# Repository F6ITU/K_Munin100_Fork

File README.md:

# MUNIN-100
MUNIN 100 is a 100W HF Power Amplifier using the MRF101AN/MRF101BN at 48V DC supply voltage.

Munin amps belongs to the OpenHPSDR familly

Original design by Kjell LA2NI

Some small mods by f6itu (just some kicad settings and design)

This amplifier board is part of a set consisting of a 100 W LD-Mos based RF power amplifier (Munin 100), 
a medium power Zolotarev low pass filter (600 or 1500 W), an Automatic Antenna Tuner (ATU) nickname « Aries » 
and a 4 port antenna switch.

But the power level is compatible with the traditional "Alexiares" filter frontend, (https://wiki.electrolab.fr/Projets:Lab:2017:Peripheriques_Angelia )
in lpf/hpf configuration or it's up to date evolution (lpf and dual bpf) 

All these developments are the work and intellectual property of Kjell Karlsen LA2NI and Laurence Barker G8NJJ.

This original work can be downloaded from

https://github.com/LA2NI/

https://github.com/laurencebarker

This board was originally developed in 2022 by Kjell LA2NI.

This fork (convertion/translation) is placed under the CERN Open source/ Open hardware Licence.

Kicad is an Opensource EDA software maintained by the European Reseach Center CERN (Conseil européen pour la recherche nucléaire)

The original work is protected by the TAPR Open Hardware licence

Mythology and openHPSDR codename conventions

Munin and Hugin are the two "messenger" ravens of the Norse god Odin - just as Hermes is the messenger-god in Greek mythology, 
and the masterpiece of the OpenHPSDR architecture 

This LDMoS transistor-based amplifier brings speech over the great distances of the "Midgard" of the waves

# Work in progress

Use these files at your own risk (that's the moto of ham homebrew)

As far as I know, this amp has never been build. Some minor KiCad errors and design hickups have been fix

The  the 1:4 input impedance transformer could be replaced with a simple coax strap (with or without ferrite core) as the combined impedance of the two transistors is approximately 50 Ohms at 55 MHz. On lower frequencies, the value of Z
is determined by the value of R4-R11 (22 Ohms, not yet tested) 

the pcb has been design to accomodate two feedback techniques : 
- coupling from a "secondary" winding in the first TLT
- or direct pickup of the drain signal fia a C & R feedback circuit

Value or R16/19 should be changed accordingly 

the first TLT MUST be soldered as short as possible. That's the reason why the third beta of this pcb uses a fat power trace located on the bottom Cu side of the board. 

For more information, please consider reading 

https://ludens.cl/Electron/50Wamp/50Wamp.html

and 

https://ludens.cl/Electron/RFamps/RFamps.html

(chapter "Broadband push-pull amplifiers"

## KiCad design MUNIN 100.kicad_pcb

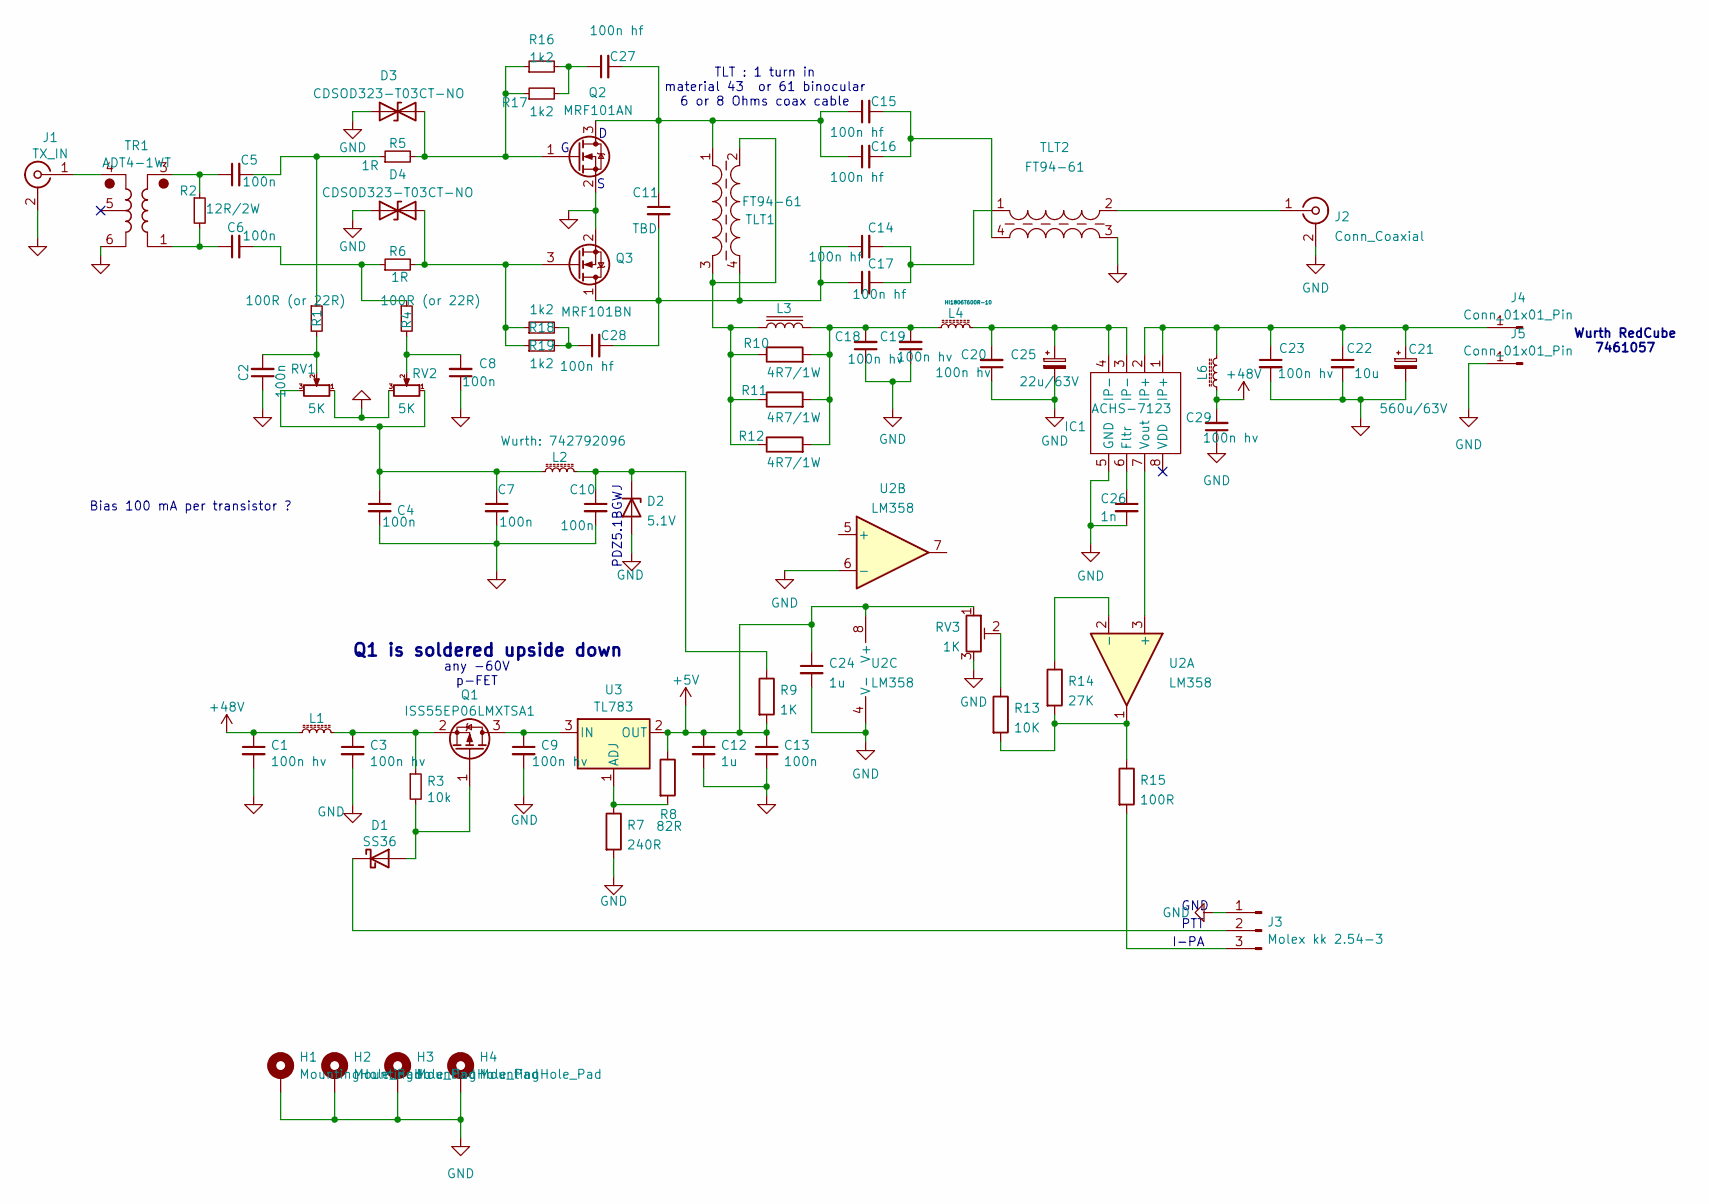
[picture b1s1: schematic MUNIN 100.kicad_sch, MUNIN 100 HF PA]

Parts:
C1, C3, C9, C18, C19, C20, C23, C29: 100n hv; C_0805_2012Metric_Pad1.18x1.45mm_HandSolder
C2, C4, C5, C6, C7, C8, C10, C13: 100n; C_0805_2012Metric_Pad1.18x1.45mm_HandSolder
C11: TBD; C_1210_3225Metric
C12, C24: 1u; C_0805_2012Metric_Pad1.18x1.45mm_HandSolder
C14, C15, C16, C17, C27, C28: 100n hf; C_1210_3225Metric_Pad1.33x2.70mm_HandSolder
C21: 560u/63V; CP_Elec_16x17.5
C22: 10u; C_0805_2012Metric_Pad1.18x1.45mm_HandSolder
C25: 22u/63V; CP_Elec_10x14.3
C26: 1n; C_0805_2012Metric_Pad1.18x1.45mm_HandSolder
D1: SS36; D_SOD-323_HandSoldering
D2: 5.1V; D_SOD-123F
D3, D4: CDSOD323-T03CT-NO; D_0805_2012Metric
H1, H2, H3, H4: MountingHole_Pad; MountingHole_3.2mm_M3_Pad_Via
IC1: ACHS-7123; SO-8_5.3x6.2mm_P1.27mm
J1: TX_IN; SMA_PINS
J2: Conn_Coaxial; SMA_PINS
J3: Molex kk 2.54-3; Molex_KK-254_AE-6410-03A_1x03_P2.54mm_Vertical
J4, J5: Conn_01x01_Pin; 7461057
L1: 742792096; L_0805_2012Metric_Pad1.05x1.20mm_HandSolder
L2: Wurth: 742792096; L_0805_2012Metric_Pad1.05x1.20mm_HandSolder
L3: FT-50-43; T50_V_smd
L4: HI1806T600R-10; L_1812_4532Metric
L6: L_Core_Ferrite_Small; L_0805_2012Metric_Pad1.05x1.20mm_HandSolder
Q1: ISS55EP06LMXTSA1; SOT-23
Q2: MRF101AN; TO-220-3_Horizontal_TabDown_SMD
Q3: MRF101BN; TO-220-3_Horizontal_TabDown_SMD
R1, R4: 100R (or 22R); R_0805_2012Metric_Pad1.20x1.40mm_HandSolder
R2: 12R/2W; R_2512_6332Metric
R3: 10k; R_0805_2012Metric_Pad1.20x1.40mm_HandSolder
R5, R6: 1R; R_0805_2012Metric_Pad1.20x1.40mm_HandSolder
R7: 240R; R_0805_2012Metric_Pad1.20x1.40mm_HandSolder
R8: 82R; R_0805_2012Metric_Pad1.20x1.40mm_HandSolder
R9: 1K; R_0805_2012Metric_Pad1.20x1.40mm_HandSolder
R10, R11, R12: 4R7/1W; R_1210_3225Metric
R13: 10K; R_0805_2012Metric_Pad1.20x1.40mm_HandSolder
R14: 27K; R_0805_2012Metric_Pad1.20x1.40mm_HandSolder
R15: 100R; R_0805_2012Metric_Pad1.20x1.40mm_HandSolder
R16, R17, R18, R19: 1k2; R_1206_3216Metric
RV1, RV2: 5K; Potentiometer_Bourns_3214X_Vertical
RV3: 1K; Potentiometer_Bourns_3214X_Vertical
TLT1: FT94-61; TLT
TLT2: FT94-61; Dual_FB-61-4852
TR1: ADT4-1WT; Mini-Circuits_CD542_H2.84mm
U2: LM358; SOIC-8_3.9x4.9mm_P1.27mm
U3: TL783; TO-263-3_TabPin2

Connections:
+5V: C12.1, C13.1, C24.1, R8.1, R9.2, RV3.1, U2.8 (V+), U3.2 (OUT)
+48V: C1.1, C29.2, L1.1, L6.1
GND: C1.2, C2.1, C3.2, C4.2, C7.2, C8.1, C9.2, C10.2, C12.2, C13.2, C18.1, C19.1, C20.1, C21.2, C22.2, C23.2, C24.2, C25.2, C26.2, C29.1, D2.2 (A), D3.1 (A1), D4.1 (A1), H1.1, H2.1, H3.1, H4.1, IC1.5 (GND), J1.2 (Ext), J2.2 (Ext), J3.1, J5.1, Q2.2 (S), Q3.2 (S), R7.2, RV1.1, RV2.3, RV3.3, TLT2.3, TR1.6, U2.4 (V-), U2.6 (-)
unnamed: C2.2, R1.2, RV1.2
unnamed: C4.1, C7.1, L2.1, RV1.3, RV2.1
unnamed: C5.1, R2.1, TR1.3
unnamed: C5.2, R1.1, R5.1
unnamed: C6.1, R2.2, TR1.1
unnamed: C6.2, R4.1, R6.1
unnamed: C8.2, R4.2, RV2.2
unnamed: C14.2, C17.2, TLT2.1
unnamed: C15.2, C16.2, TLT2.4
unnamed: C18.2, C19.2, L3.2, L4.1, R10.2, R11.2, R12.2
unnamed: C20.2, C25.1, IC1.3 (IP-), IC1.4 (IP-), L4.2
unnamed: C27.1, R16.2, R17.2
unnamed: C28.1, R18.2, R19.2
unnamed: D1.2 (A), Q1.1 (G), R3.2
unnamed: D1.1 (K), J3.2
unnamed: C10.1, D2.1 (K), L2.2, R9.1
unnamed: D3.2 (A2), Q2.1 (G), R5.2, R16.1, R17.1
unnamed: D4.2 (A2), Q3.3 (G), R6.2, R18.1, R19.1
unnamed: C26.1, IC1.6 (Fltr)
unnamed: IC1.7 (Vout), U2.3 (+)
unnamed: J1.1 (In), TR1.4
unnamed: J2.1 (In), TLT2.2
unnamed: J3.3, R15.2
unnamed: C21.1, C22.1, C23.1, IC1.1 (IP+), IC1.2 (IP+), J4.1, L6.2
unnamed: L3.1, R10.1, R11.1, R12.1, TLT1.2, TLT1.3
unnamed: C9.1, Q1.3 (D), U3.3 (IN)
unnamed: C3.1, L1.2, Q1.2 (S), R3.1
unnamed: C11.1, C15.1, C16.1, C27.2, Q2.3 (D), TLT1.1
unnamed: C11.2, C14.1, C17.1, C28.2, Q3.1 (D), TLT1.4
unnamed: R13.1, RV3.2
unnamed: R13.2, R14.2, R15.1, U2.1
unnamed: R14.1, U2.2 (-)
unnamed: R7.1, R8.2, U3.1 (ADJ)

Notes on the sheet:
Q1 is soldered upside down
PDZ5.1BGWJ
GND
TLT : 1 turn in material 43 or 61 binocular 6 or 8 Ohms coax cable
PTT
Bias 100 mA per transistor ?
Wurth RedCube 7461057
I-PA
any -60V p-FET

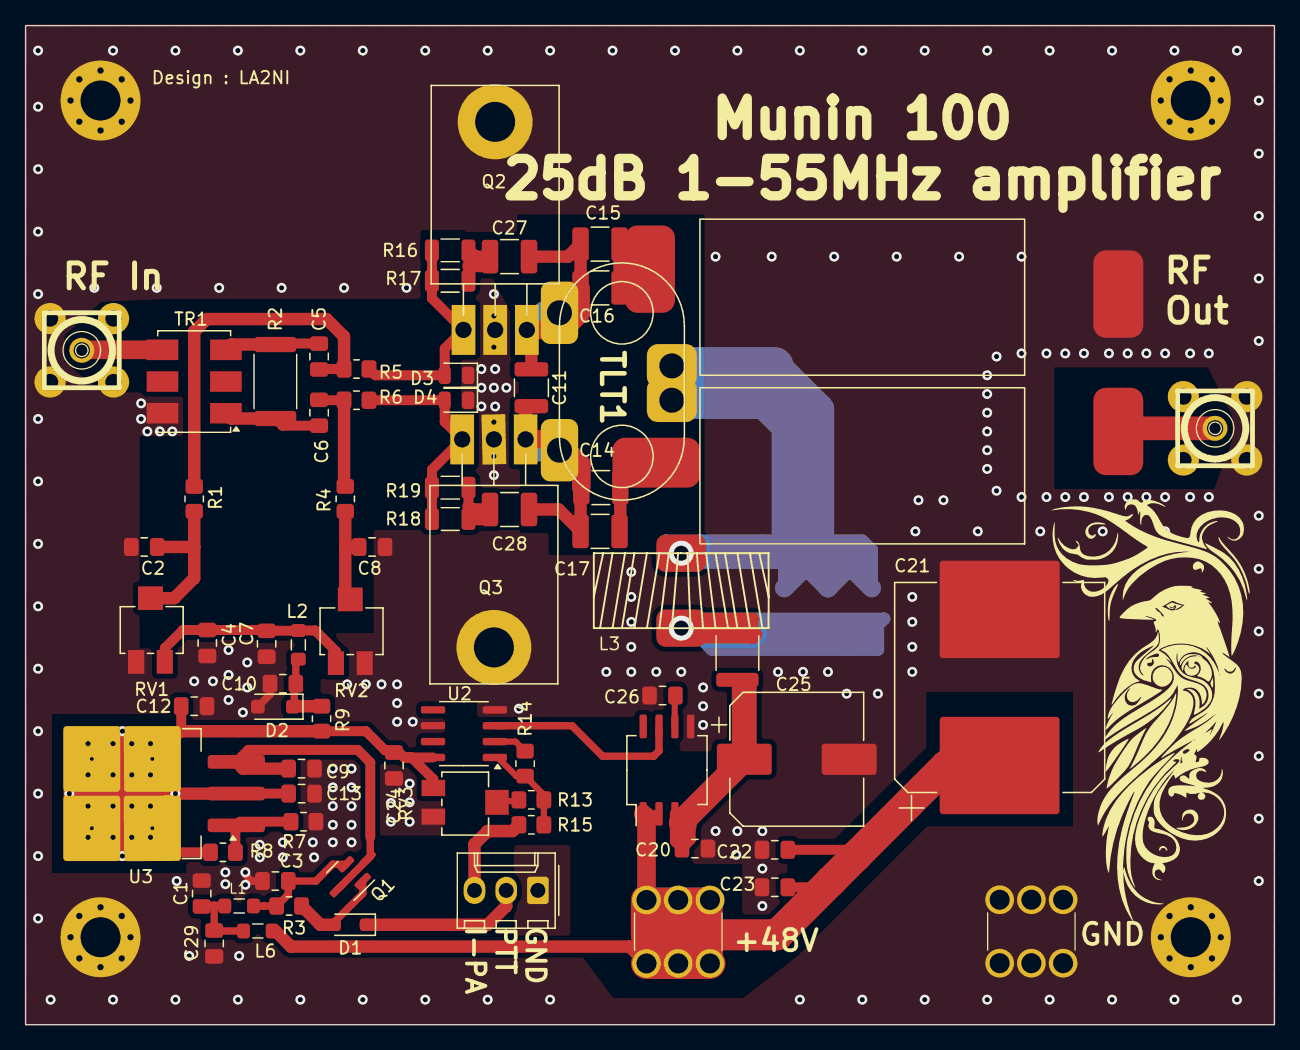
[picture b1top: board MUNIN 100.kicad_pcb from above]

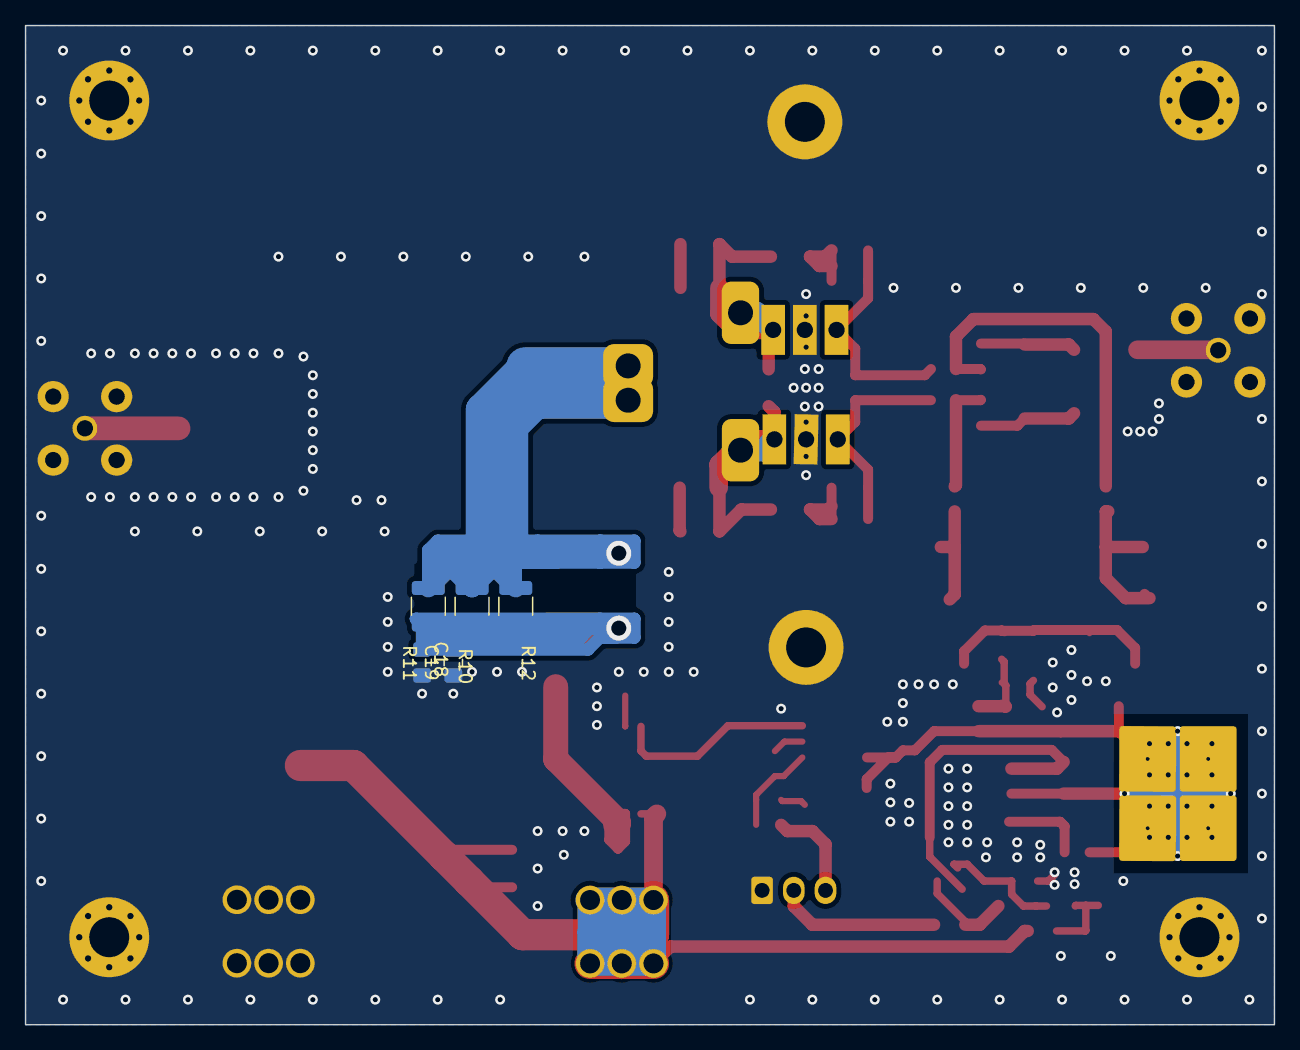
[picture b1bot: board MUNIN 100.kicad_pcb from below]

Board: 2 copper layers, 100.0 x 80.0 mm, 78 parts (5 on the bottom side), 36 nets.

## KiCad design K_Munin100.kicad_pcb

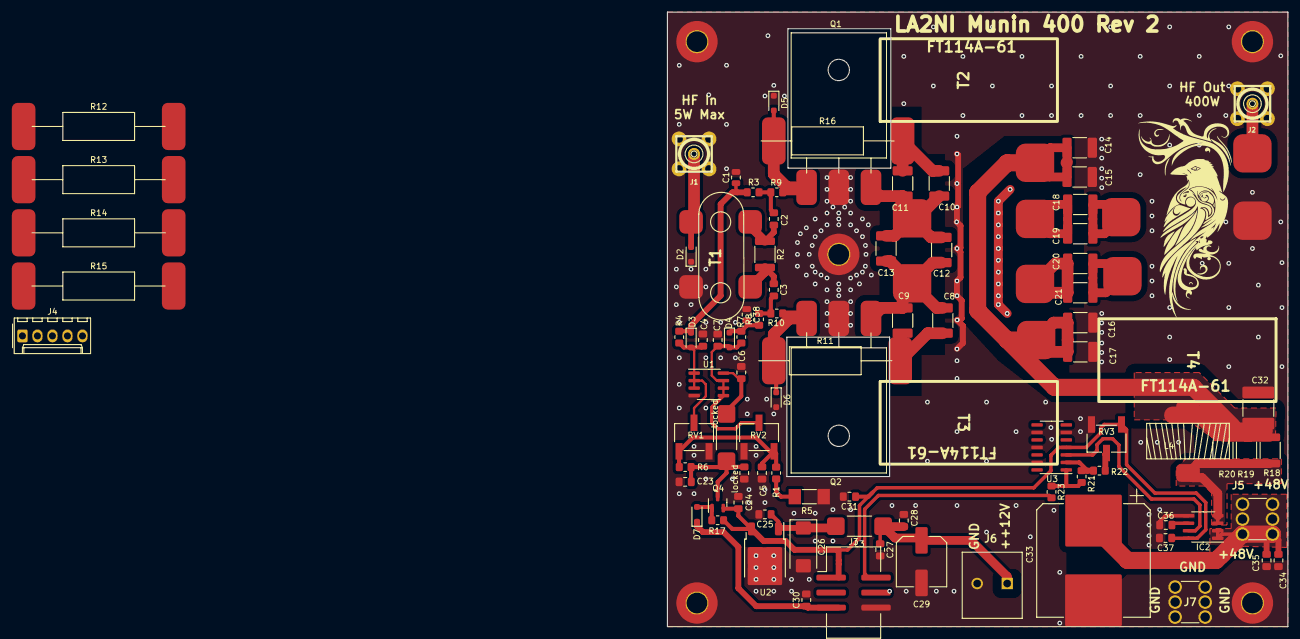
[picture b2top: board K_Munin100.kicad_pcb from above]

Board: 2 copper layers, 105.0 x 104.0 mm, 96 parts (0 on the bottom side), 39 nets.

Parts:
C1, C38: 100n; C_0805_2012Metric
C2, C3, C30: 10n; C_0805_2012Metric_Pad1.18x1.45mm_HandSolder
C4, C5, C7, C27, C28, C35: 100n; C_0805_2012Metric_Pad1.18x1.45mm_HandSolder
C6, C23, C24, C25, C31, C34, C37: 1u; C_0805_2012Metric_Pad1.18x1.45mm_HandSolder
C8, C11: 1u/250V; C_1812_4532Metric_Pad1.57x3.40mm_HandSolder
C9, C10: 10n/250V; C_1812_4532Metric_Pad1.57x3.40mm_HandSolder
C12, C13: TBD; C_1812_4532Metric_Pad1.57x3.40mm_HandSolder
C14, C15, C16, C17, C18, C19, C20, C21: 100n; C_1812_4532Metric_Pad1.57x3.40mm_HandSolder
C26: 10u; CP_EIA-7343-31_Kemet-D_Pad2.25x2.55mm_HandSolder
C29: 220u; C_Elec_8x10.2
C32: 22u/63V; C_2220_5650Metric_Pad1.97x5.40mm_HandSolder
C33: 330u/63V; CP_Elec_18x17.5
C36: 1n; C_0805_2012Metric_Pad1.18x1.45mm_HandSolder
D2: CDSOD323-TC15; D_SOD-323_HandSoldering
D3, D4, D7: BAS16J; D_SOD-323_HandSoldering
D5, D6: CDSOD323-TC03; D_SOD-323_HandSoldering
H1, H2, H3, H4, H5: MountingHole_Pad; MountingHole_3.5mm_Pad_TopBottom
IC2: ACHS-7123-000E; SOIC-8_3.9x4.9mm_P1.27mm
J1, J2: Conn_Coaxial; SMA_PINS
J3: Conn_02x03_Odd_Even; IDC-Header_2x03_P2.54mm_Vertical_SMD
J4: To P.A.; Molex_KK-254_AE-6410-05A_1x05_P2.54mm_Vertical
J5, J7: Wurth Redcube 7461057; 7461057
J6: Phoenix/1711725; 1711725
L3: 2743021447; Fair-Rite_2743021447
L4: FT82-61?; T50_V_smd
Q1: MRF300AN tab dwn; TO-247-3_Horizontal_TabDown
Q2: MRF300BN tab up; TO-247-3_Horizontal_TabUp
Q4: BSS84; SOT-23
R1: 6K8; R_0805_2012Metric_Pad1.20x1.40mm_HandSolder
R2: 5R6; R_1812_4532Metric_Pad1.30x3.40mm_HandSolder
R3, R8: 22R; R_0805_2012Metric_Pad1.20x1.40mm_HandSolder
R4, R7: 220R; R_0805_2012Metric_Pad1.20x1.40mm_HandSolder
R5: NTC10K; R_MELF_MMB-0207
R6: 1.2k; R_0805_2012Metric_Pad1.20x1.40mm_HandSolder
R9, R10: 1R; R_0805_2012Metric_Pad1.20x1.40mm_HandSolder
R11, R12, R13, R14, R15, R16: 470R; R_Axial_DIN0414_L11.9mm_D4.5mm_P25.40mm_Horizontal
R17, R22: 10k; R_0805_2012Metric_Pad1.20x1.40mm_HandSolder
R18, R19, R20: 4R7; R_1812_4532Metric_Pad1.30x3.40mm_HandSolder
R21: 27k; R_0805_2012Metric_Pad1.20x1.40mm_HandSolder
R23: 100R; R_0805_2012Metric_Pad1.20x1.40mm_HandSolder
RV1, RV2: 10k; Potentiometer_Bourns_3269W_Vertical
RV3: 1k; Potentiometer_Bourns_3269W_Vertical
T1: BN43-202 3:1; BN43-202
T2: 5961001201; FT114A-61
T3: 5961001201; FT114A-61_B
T4: 5961001201; FT114A-61_out
U1: LM358; SOIC-8_3.9x4.9mm_P1.27mm
U2: LM78M05_TO252; TO-252-2
U3: LMC660AIM_NOPB; SOIC-14_3.9x8.7mm_P1.27mm
locked: 100n; C_0805_2012Metric_Pad1.18x1.45mm_HandSolder
locked#2: 2743021447; Fair-Rite_2743021447

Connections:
5V: C24.1, C31.1, C37.1, IC2.8 (VDD), J3.1, J4.2, Q4.2 (S), R17.2, RV3.1, U2.3 (VO), U3.4 (V+)
+12V: C27.1, C28.1, C29.1, J6.1, L3.1
+48V: C33.1, C34.1, C35.1, IC2.1 (IP+_1), IC2.2 (IP+_2), J5.1
A6: J3.2, J4.1, R23.2
GND: C1.2, C4.2, C5.2, C6.2, C7.2, C14.2, C15.2, C16.2, C17.2, C23.2, C24.2, C25.2, C26.2, C27.2, C28.2, C29.2, C30.2, C31.2, C32.2, C33.2, C34.2, C35.2, C36.2, C37.2, C38.1, D2.1 (A1), D5.1 (A1), D6.2 (A2), H1.1, H2.1, H3.1, H4.1, H5.1, IC2.5 (GND), J1.2 (Ext), J2.2 (Ext), J3.6, J4.5, J6.2, J7.1, Q1.2 (S), Q2.2 (S), R5.2, RV1.3, RV2.1, RV3.3, T1.2 (AB), T4.2 (AB), U1.4 (V-), U2.2 (GND), U3.6 (-), U3.9 (-), U3.11 (V-), U3.13 (-), locked.2
unnamed: C2.2, R3.1, R9.1
unnamed: C3.2, R8.1, R10.1
unnamed: C5.1, R1.1, R6.1, RV1.1, RV2.3
unnamed: C8.2, C9.2, R11.2, R12.2, R13.2
unnamed: C10.2, C11.2, R14.2, R15.2, R16.2
unnamed: D2.2 (A2), J1.1 (In), T1.1 (AA)
unnamed: C4.1, D3.2 (A), R4.2, RV1.2, U1.1, U1.2 (-), U1.3 (+)
unnamed: C1.1, D3.1 (K), R3.2, R4.1
unnamed: C7.1, D4.2 (A), R7.2, RV2.2, U1.5 (+), U1.6 (-), U1.7
unnamed: C38.2, D4.1 (K), R7.1, R8.2
unnamed: D5.2 (A2), Q1.1 (G), R9.2, R14.1, R15.1, R16.1
unnamed: D6.1 (A1), Q2.1 (G), R10.2, R11.1, R12.1, R13.1
unnamed: D7.2 (A), Q4.1 (G), R17.1
unnamed: C36.1, IC2.6 (FILTER)
unnamed: IC2.3 (IP-_1), IC2.4 (IP-_2), L4.1, R18.2, R19.2, R20.2
unnamed: IC2.7 (VOUT), U3.3 (+)
unnamed: J2.1 (In), T4.3 (SA)
unnamed: C10.1, C11.1, C12.2, C13.2, Q1.3 (D), T2.3 (SB), T3.1 (AA)
unnamed: C8.1, C9.1, C12.1, C13.1, Q2.3 (D), T2.1 (AA), T3.3 (SB)
unnamed: C23.1, Q4.3 (D), R6.2, locked.1, locked#2.2
unnamed: R1.2, R5.1
unnamed: R21.2, R23.1, U3.1
unnamed: R22.1, RV3.2
unnamed: C3.1, R2.2, T1.3 (SA)
unnamed: C2.1, R2.1, T1.4 (SB)
unnamed: C18.1, C19.1, T2.2 (AB)
unnamed: C14.1, C15.1, C16.1, C17.1, C32.1, L4.2, R18.1, R19.1, R20.1, T2.4 (SA), T3.4 (SA)
unnamed: C20.1, C21.1, T3.2 (AB)
unnamed: C20.2, C21.2, T4.1 (AA)
unnamed: C18.2, C19.2, T4.4 (SB)
unnamed: C6.1, U1.8 (V+), locked#2.1
unnamed: C25.1, C26.1, L3.2, U2.1 (VI)
unnamed: R21.1, R22.2, U3.2 (-)
PTT_IN: C30.1, D7.1 (K), J3.5, J4.4

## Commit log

2024-04-21 Munin 400 mod with MRF101 AN/BN
2024-04-25 former fork outdated, LA2NI's amp used as main
2024-04-29 first pcb release
2024-05-14 ibom and gerber added, first prototype
2024-06-05 minor errors fixed, Gerber is out of date
2024-06-23 new 48V trace
2024-06-26 48V rail, kicad 8.03, no new gerber
2024-11-19 third release, new power TLT
2026-03-23 kicad10 update, minor schematic changes
